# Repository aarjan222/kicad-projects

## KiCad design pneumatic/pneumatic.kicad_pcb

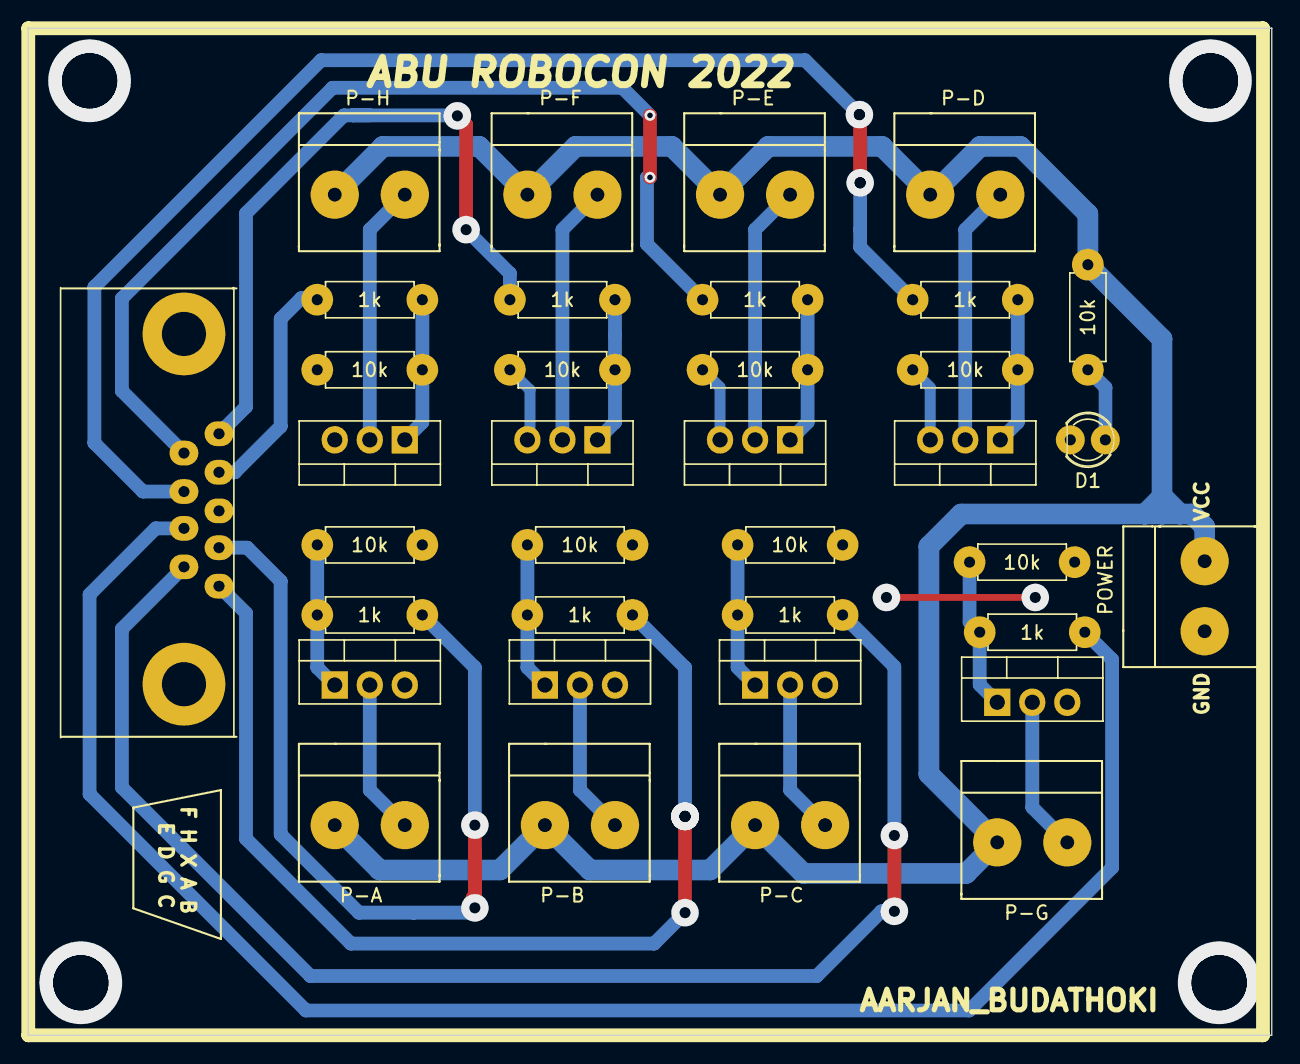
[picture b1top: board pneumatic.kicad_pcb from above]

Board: 2 copper layers, 90.2 x 73.0 mm, 36 parts (1 on the bottom side), 27 nets.

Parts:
D1: LED; LED_D3.0mm
J3: DB9_Female_MountingHoles; Connector_DB_9
P-A: Conn_01x02_Female; Connector_Bornier_2
P-B: Conn_01x02_Female; Connector_Bornier_2
P-C: Conn_01x02_Female; Connector_Bornier_2
P-D: Conn_01x02_Female; Connector_Bornier_2
P-E: Conn_01x02_Female; Connector_Bornier_2
P-F: Conn_01x02_Female; Connector_Bornier_2
P-G: Conn_01x02_Female; Connector_Bornier_2
P-H: Conn_01x02_Female; Connector_Bornier_2
POWER: Conn_01x02_Female; Connector_Bornier_2
Q2, Q3, Q4, Q5, Q6, Q7, Q8, Q9: TIP122; TO-220-3_Vertical
R1, R6, R7, R8, R9, R14, R15, R16, R17: 10k; Resistor_small
R2, R3, R4, R5, R10, R11, R12, R13: 1k; Resistor_small

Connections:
/12V: P-A.1, P-B.1, P-C.1, P-D.1, P-E.1, P-F.1, P-G.1, P-H.1, POWER.2, R1.1
/A: J3.2, R2.1
/B: J3.1, R4.1
/C: J3.6, R5.1
/D: J3.8, R3.1
/E: J3.9, R10.1
/F: J3.5, R12.1
/G: J3.7, R13.1
/H: J3.4, R11.1
GND: D1.1 (K), POWER.1, Q2.3 (E), Q3.3 (E), Q4.3 (E), Q5.3 (E), Q6.3 (E), Q7.3 (E), Q8.3 (E), Q9.3 (E), R6.1, R7.1, R8.1, R9.1, R14.1, R15.1, R16.1, R17.1
unnamed: D1.2 (A), R1.2
unnamed: P-A.2, Q2.2 (C)
unnamed: P-D.2, Q3.2 (C)
unnamed: P-B.2, Q4.2 (C)
unnamed: P-C.2, Q5.2 (C)
unnamed: P-E.2, Q6.2 (C)
unnamed: P-H.2, Q7.2 (C)
unnamed: P-F.2, Q8.2 (C)
unnamed: P-G.2, Q9.2 (C)
unnamed: Q2.1 (B), R2.2, R6.2
unnamed: Q3.1 (B), R3.2, R7.2
unnamed: Q4.1 (B), R4.2, R8.2
unnamed: Q5.1 (B), R5.2, R9.2
unnamed: Q6.1 (B), R10.2, R14.2
unnamed: Q7.1 (B), R11.2, R15.2
unnamed: Q8.1 (B), R12.2, R16.2
unnamed: Q9.1 (B), R13.2, R17.2
